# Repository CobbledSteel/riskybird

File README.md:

# RiskyBird for ROAR-Academy

This is the tutorial created by [Dima Nikiforov](https://www.linkedin.com/in/dima) and [Kris Dong](https://www.linkedin.com/in/chris-dong/) for ROAR Academy. The material has been taught at the University of California, Berkeley, as part of Berkeley ROAR Racing curriculum to students who want to learn entry-level skills about:

* Introduction to Embedded Systems
* Machine Learning Programming on Edge device 
* Introduction to Robotics
* Scientific Programming and Quantization
* Deep Neural Networks (DNN)
* Reinforcement Learning (RL) 

The material has been made open source FOR NON-COMMERCIAL USE only. Please contact the author for any questions: <vnikiforov@berkeley.edu>, <krisdong@berkeley.edu>

## Basic Installation

Users of this course are recommended to install the following software packages. The packages have been tested on Windows 10 and above, Mac OSX, and Ubuntu Linux systems.

* Python 3.8 via Miniconda (conda): <https://docs.conda.io/en/latest/miniconda.html>
* Git: <https://git-scm.com/book/en/v2/Getting-Started-Installing-Git>
* Visual Studio Code (code): <https://code.visualstudio.com/download>

**NOTE: If you are running conda and code in Windows, launching code from Anaconda Prompt will make sure that the conda environment available inside the integrated Terminal window. Otherwise you may encounter error that conda is not installed**

Once Python 3.8 is installed, the following Python modules can be installed using pip within the conda environment (for example, in (base) environment):
~~~
    python -m pip install numpy matplotlib
~~~

## Tensorflow Installation for Windows and Linux

For the DNN portion, we use tensorflow 2 and keras. The installation shall reference the official documentation: <https://www.tensorflow.org/install>. 

**Due to the fact that Google stopped supporing Windows Native environment above tensorflow 2.10, please make sure to install and use tensorflow 2.10 for compatibility with our tested code**

**If your PC comes with supported NVidia GPU for accelerating DNN code, please follow carefully the setup of GPU support for Linux and Windows Native. For MacOS, please read the instruction at the end**

After you have setup your system for an installation on either CPU or GPU, run the following pip script to install tensorflow 2.10
~~~
    pip install --upgrade pip
    pip install tensorflow==2.10
    pip install numpy==1.21
~~~

Finally, you may verify tensorflow has been properly set up by running the following test
~~~
    python -c "import tensorflow as tf; print(tf.reduce_sum(tf.random.normal([1000, 1000])))"
~~~

If you have install tensorflow with GPU support, you may verify by running the following test
~~~
    python -c "import tensorflow as tf; print(tf.config.list_physical_devices('GPU'))"
~~~

## Tensorflow Installation with Metal accelerated backend for MacOS

Apple has released a Metal-accelerated tensorflow backend to utilize the GPU on MacOS. Please visit Apple website to install tensorflow 2.10: <https://developer.apple.com/metal/tensorflow-plugin/>

## Installation of Reinforcement Learning Modules

This course will require installation of the following reinforcement learning modules:

* gym simulator: <https://github.com/openai/gym>
~~~
 pip install gym==0.17.3
 pip install pyglet==1.5.11
~~~

* gym-pybullet-drones simulator
~~~
 git submodule update --init --recursive
 cd sim/gym-pybullet-drones/
 pip3 install --upgrade pip
 pip3 install -e .
 pip3 install pyserial
~~~

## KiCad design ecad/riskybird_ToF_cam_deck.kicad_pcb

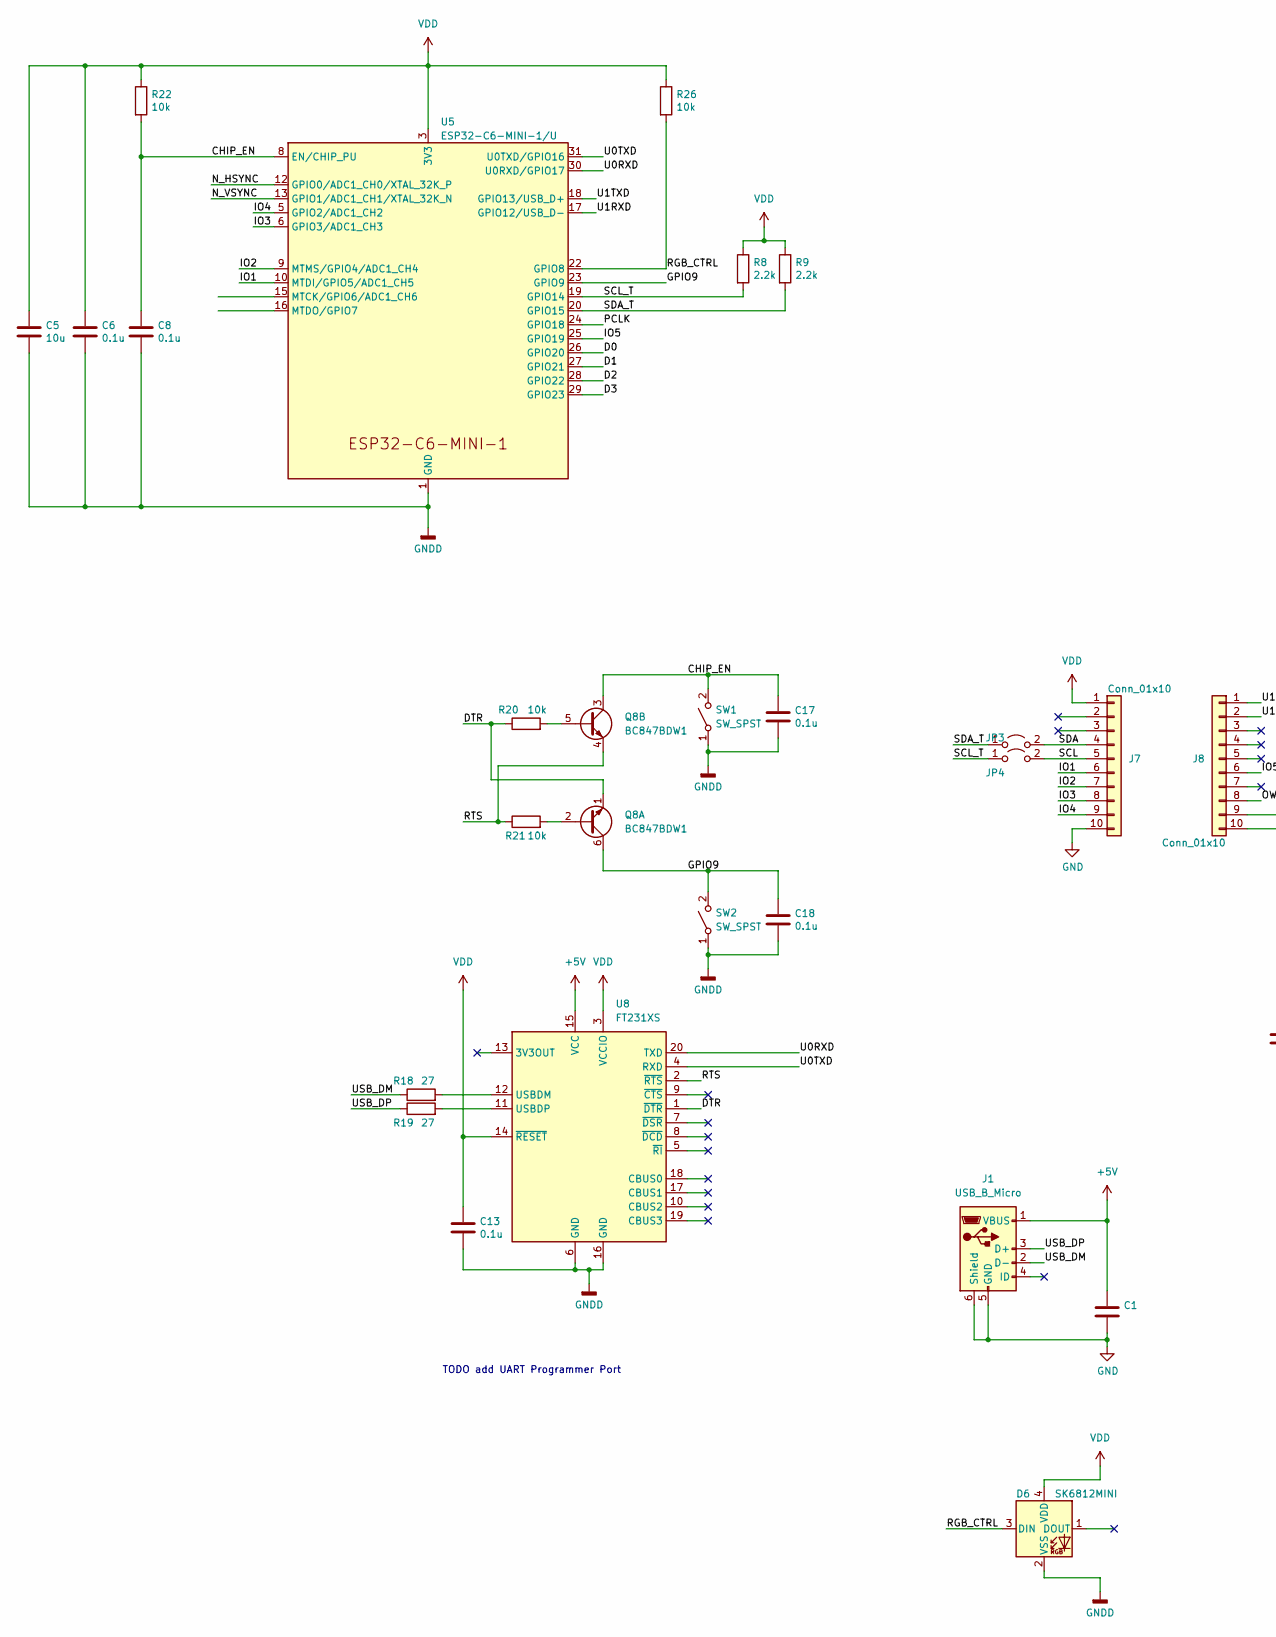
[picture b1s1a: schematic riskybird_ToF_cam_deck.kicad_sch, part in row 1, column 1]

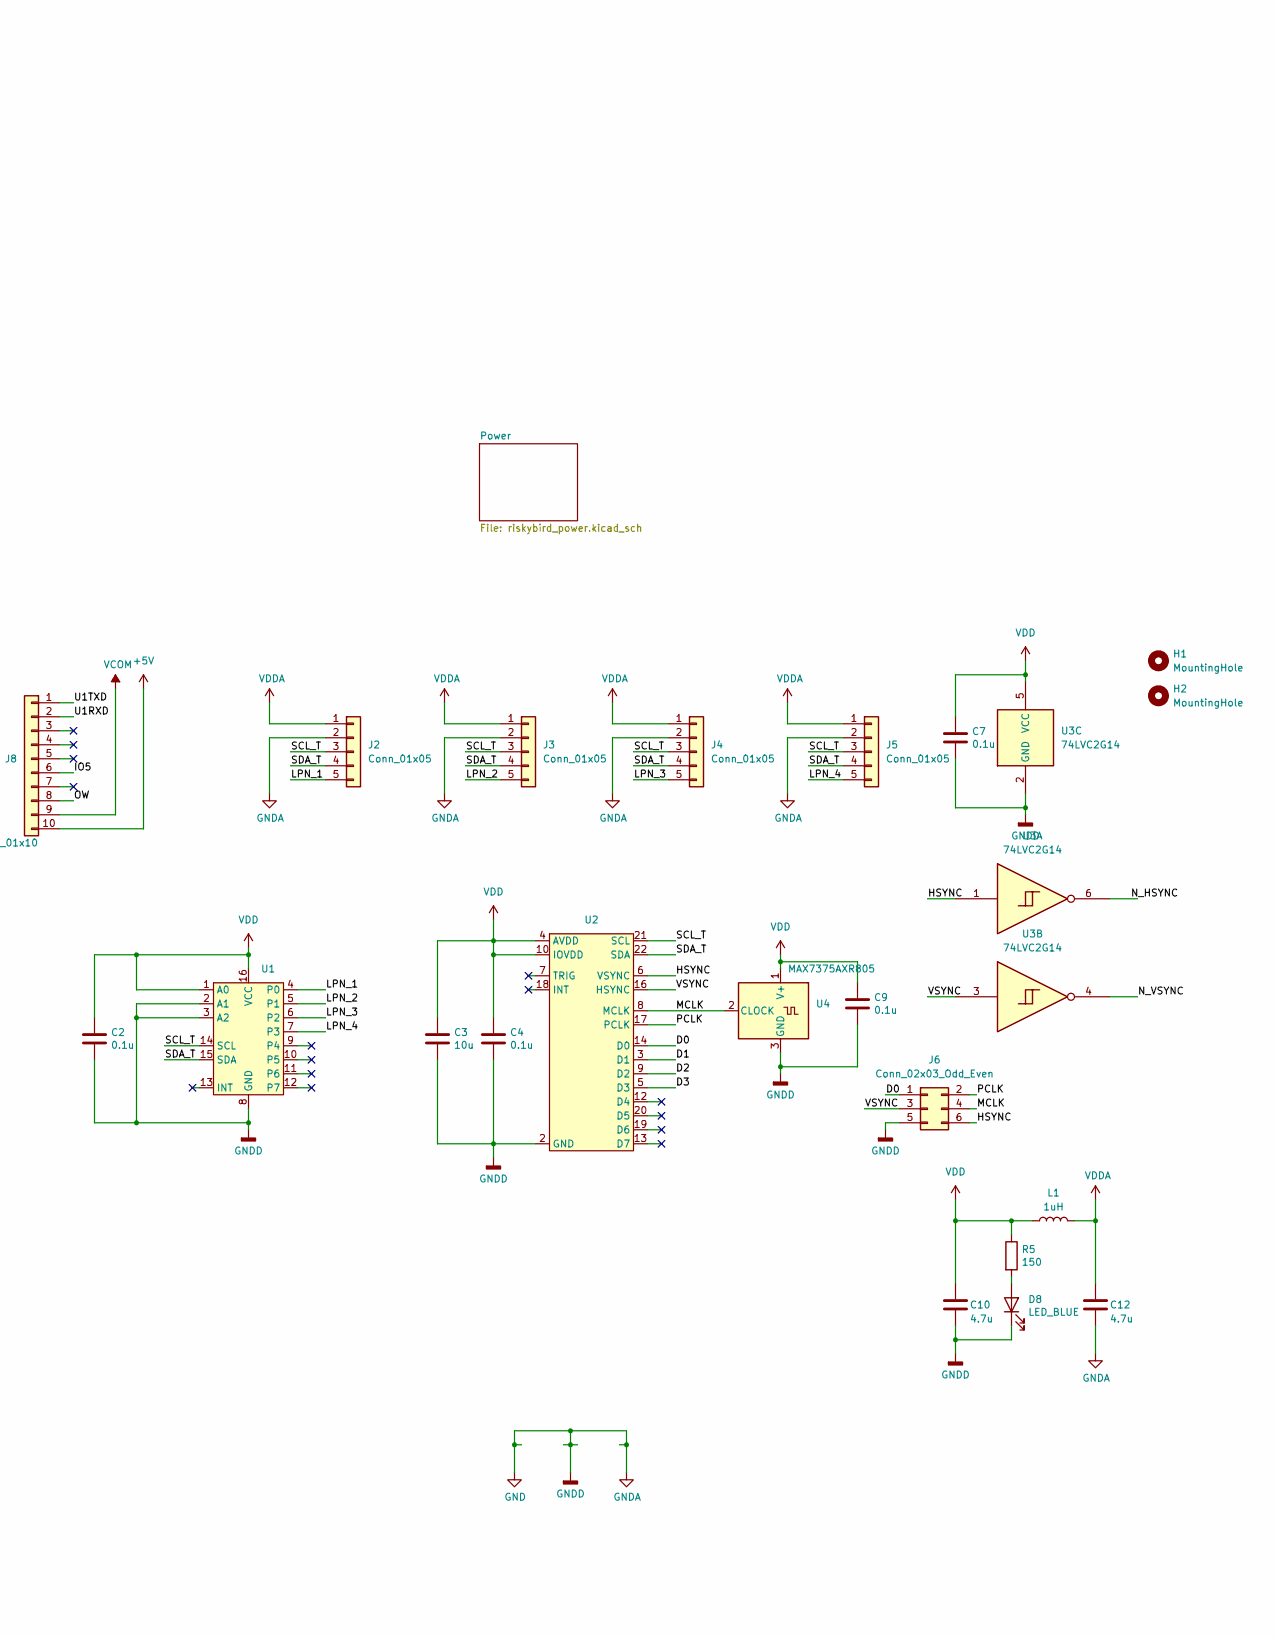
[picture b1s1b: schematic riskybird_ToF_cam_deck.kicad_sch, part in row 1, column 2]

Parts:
C1, C10, C12: 4.7u; C_0402_1005Metric
C2, C4, C6, C7, C8, C9, C13, C17, C18: 0.1u; C_0402_1005Metric
C3, C5: 10u; C_0402_1005Metric
D6: SK6812MINI; LED_SK6812MINI_PLCC4_3.5x3.5mm_P1.75mm
D8: LED_BLUE; LED_0805_2012Metric_Pad1.15x1.40mm_HandSolder
H1, H2: MountingHole; MountingHole_2.2mm_M2
J1: USB_B_Micro; USB_Micro-B_Molex_47346-0001
J2, J3, J4, J5: Conn_01x05; PinHeader_1x05_P2.54mm_Vertical
J6: Conn_02x03_Odd_Even; PinHeader_2x03_P1.27mm_Vertical
J7, J8: Conn_01x10; PinHeader_1x10_P2.00mm_Vertical_SMD_Pin1Right_THT
JP3, JP4: Jumper_2_Open; R_0402_1005Metric
L1: 1uH; L_0402_1005Metric
Q8: BC847BDW1; SOT-363_SC-70-6
R5: 150; R_0402_1005Metric
R8, R9: 2.2k; R_0402_1005Metric
R18, R19: 27; R_0402_1005Metric
R20, R21, R22, R26: 10k; R_0402_1005Metric
SW1, SW2: SW_SPST; SW_SPST_B3U-1000P
U1: TSSOP-16_4.4x5mm_P0.65mm
U2: SFV24R-1STE1LF
U3: 74LVC2G14; SOT-23-6
U4: MAX7375AXR805; SOT-323_SC-70
U5: ESP32-C6-MINI-1/U; ESP32-C6-MINI-1
U8: FT231XS; SSOP-20_3.9x8.7mm_P0.635mm

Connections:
+5V: C1.1, J1.1 (VBUS), J8.10, U8.15 (VCC)
/CHIP_EN: C8.1, C17.1, Q8.3 (C2), R22.2, SW1.2 (B), U5.8 (EN/CHIP_PU)
/D0: J6.1, U2.14 (D0), U5.26 (GPIO20)
/D1: U2.3 (D1), U5.27 (GPIO21)
/D2: U2.9 (D2), U5.28 (GPIO22)
/D3: U2.5 (D3), U5.29 (GPIO23)
/DTR: Q8.1 (E1), R20.1, U8.1 (~DTR)
/GPIO9: C18.1, Q8.6 (C1), SW2.2 (B), U5.23 (GPIO9)
/HSYNC: J6.6, U2.6 (VSYNC), U3.1
/IO1: J7.6, U5.10 (MTDI/GPIO5/ADC1_CH5)
/IO2: J7.7, U5.9 (MTMS/GPIO4/ADC1_CH4)
/IO3: J7.8, U5.6 (GPIO3/ADC1_CH3)
/IO4: J7.9, U5.5 (GPIO2/ADC1_CH2)
/IO5: J8.6, U5.25 (GPIO19)
/LPN_1: J2.5, U1.4 (P0)
/LPN_2: J3.5, U1.5 (P1)
/LPN_3: J4.5, U1.6 (P2)
/LPN_4: J5.5, U1.7 (P3)
/MCLK: J6.4, U2.8 (MCLK), U4.2 (CLOCK)
/N_HSYNC: U3.6, U5.12 (GPIO0/ADC1_CH0/XTAL_32K_P)
/N_VSYNC: U3.4, U5.13 (GPIO1/ADC1_CH1/XTAL_32K_N)
/OW: J8.8
/PCLK: J6.2, U2.17 (PCLK), U5.24 (GPIO18)
/RGB_CTRL: D6.3 (DIN), R26.2, U5.22 (GPIO8)
/RTS: Q8.4 (E2), R21.1, U8.2 (~RTS)
/SCL: J7.5, JP4.2 (B)
/SCL_T: J2.3, J3.3, J4.3, J5.3, JP4.1 (A), R8.2, U1.14 (SCL), U2.21 (SCL), U5.19 (GPIO14)
/SDA: J7.4, JP3.2 (B)
/SDA_T: J2.4, J3.4, J4.4, J5.4, JP3.1 (A), R9.2, U1.15 (SDA), U2.22 (SDA), U5.20 (GPIO15)
/U0RXD: U5.30 (U0RXD/GPIO17), U8.20 (TXD)
/U0TXD: U5.31 (U0TXD/GPIO16), U8.4 (RXD)
/U1RXD: J8.2, U5.17 (GPIO12/USB_D-)
/U1TXD: J8.1, U5.18 (GPIO13/USB_D+)
/USB_DM: J1.2 (D-), R18.1
/USB_DP: J1.3 (D+), R19.1
/VSYNC: J6.3, U2.16 (HSYNC), U3.3
GND: C1.2, C2.2, C3.2, C4.2, C5.2, C6.2, C7.2, C8.2, C9.2, C10.2, C12.2, C13.2, C17.2, C18.2, D6.2 (VSS), D8.1 (K), J1.5 (GND), J1.6 (Shield), J2.2, J3.2, J4.2, J5.2, J6.5, J7.10, SW1.1 (A), SW2.1 (A), U1.2 (A1), U1.3 (A2), U1.8 (GND), U2.2 (GND), U3.2 (GND), U4.3 (GND), U5.1 (GND), U5.2 (GND), U5.11 (GND), U5.14 (GND), U5.36 (GND), U5.37 (GND), U5.38 (GND), U5.39 (GND), U5.40 (GND), U5.41 (GND), U5.42 (GND), U5.43 (GND), U5.44 (GND), U5.45 (GND), U5.46 (GND), U5.47 (GND), U5.48 (GND), U5.49 (GND), U5.50 (GND), U5.51 (GND), U5.52 (GND), U5.53 (GND), U8.6 (GND), U8.16 (GND)
unnamed: D8.2 (A), R5.2
unnamed: Q8.2 (B1), R21.2
unnamed: Q8.5 (B2), R20.2
unnamed: R18.2, U8.12 (USBDM)
unnamed: R19.2, U8.11 (USBDP)
VCOM: J8.9
VDD: C2.1, C3.1, C4.1, C5.1, C6.1, C7.1, C9.1, C10.1, C13.1, D6.4 (VDD), J7.1, L1.1, R5.1, R8.1, R9.1, R22.1, R26.1, U1.1 (A0), U1.16 (VCC), U2.4 (AVDD), U2.10 (IOVDD), U3.5 (VCC), U4.1 (V+), U5.3 (3V3), U8.3 (VCCIO), U8.14 (~RESET)
VDDA: C12.1, J2.1, J3.1, J4.1, J5.1, L1.2

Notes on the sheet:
TODO add UART Programmer Port

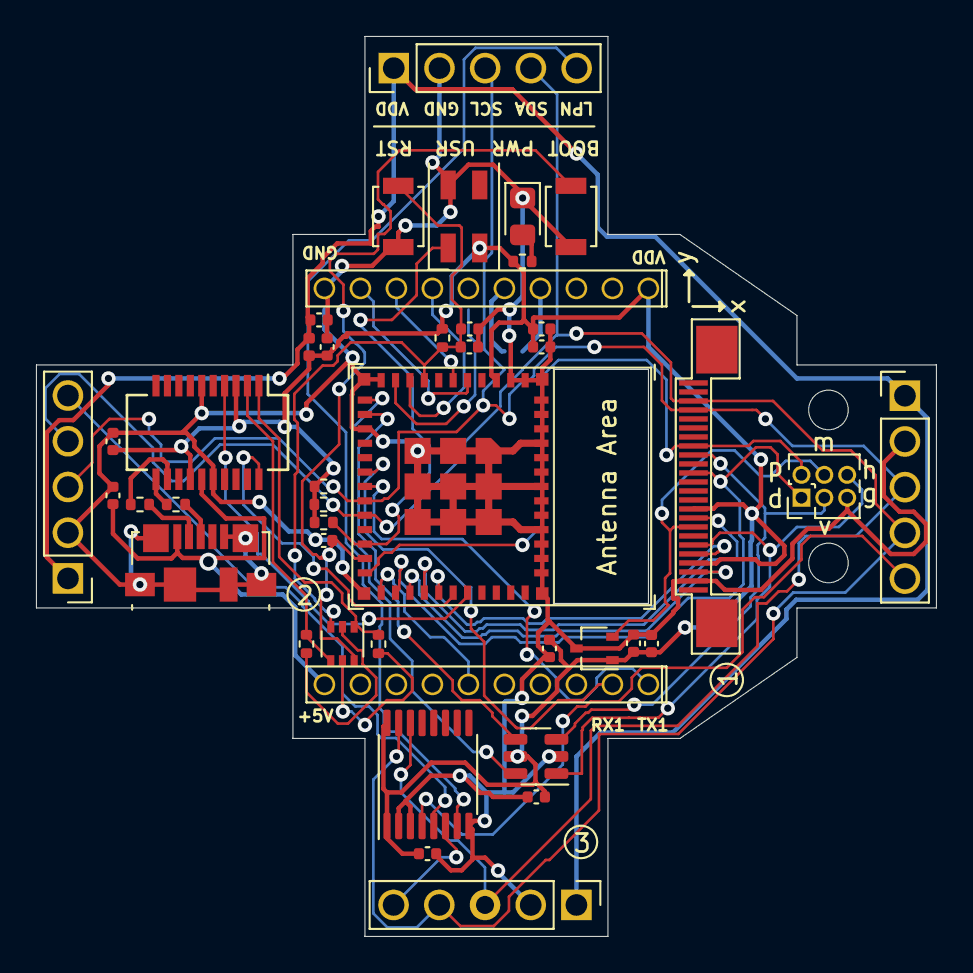
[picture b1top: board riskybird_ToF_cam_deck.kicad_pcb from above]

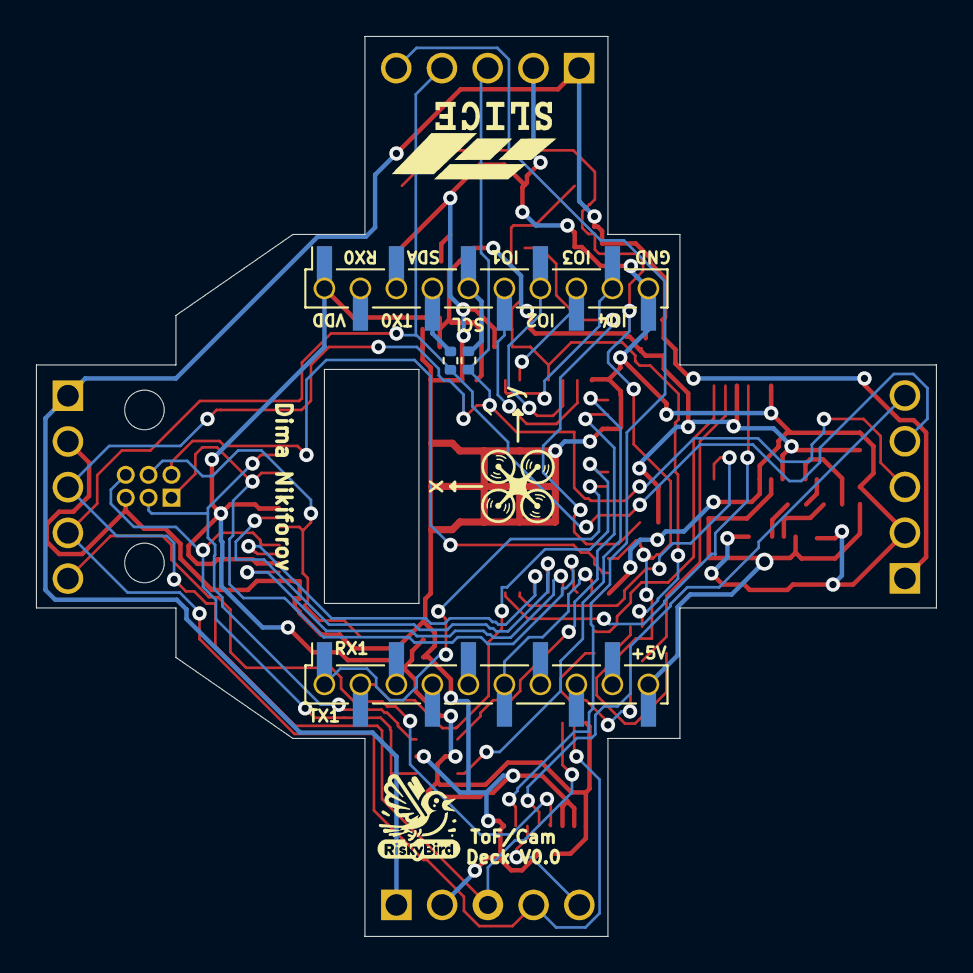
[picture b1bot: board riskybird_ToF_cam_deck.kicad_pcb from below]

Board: 2 copper layers, 50.0 x 50.0 mm, 47 parts (4 on the bottom side), 43 nets.

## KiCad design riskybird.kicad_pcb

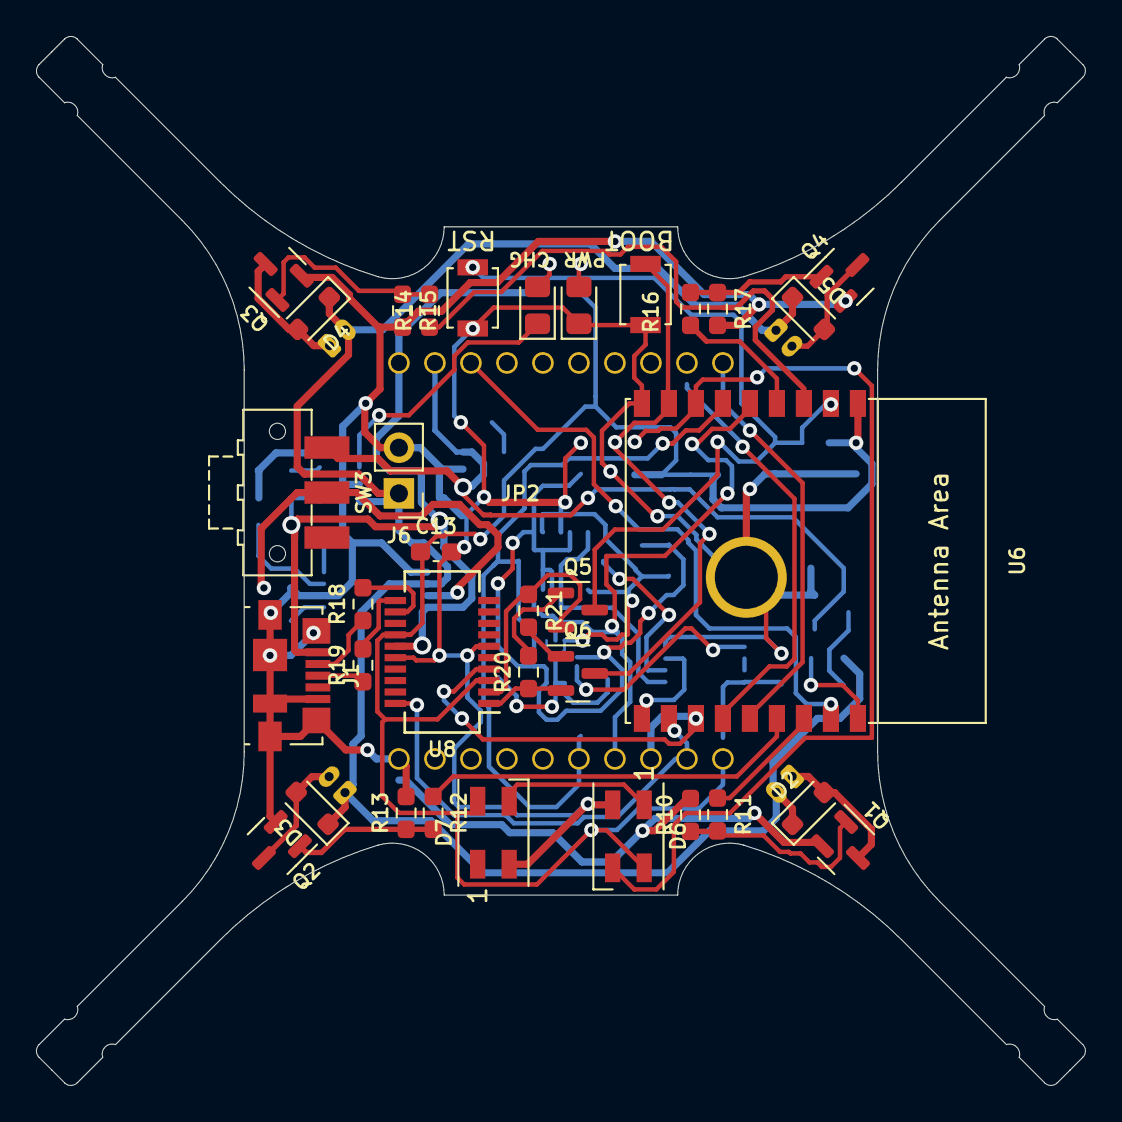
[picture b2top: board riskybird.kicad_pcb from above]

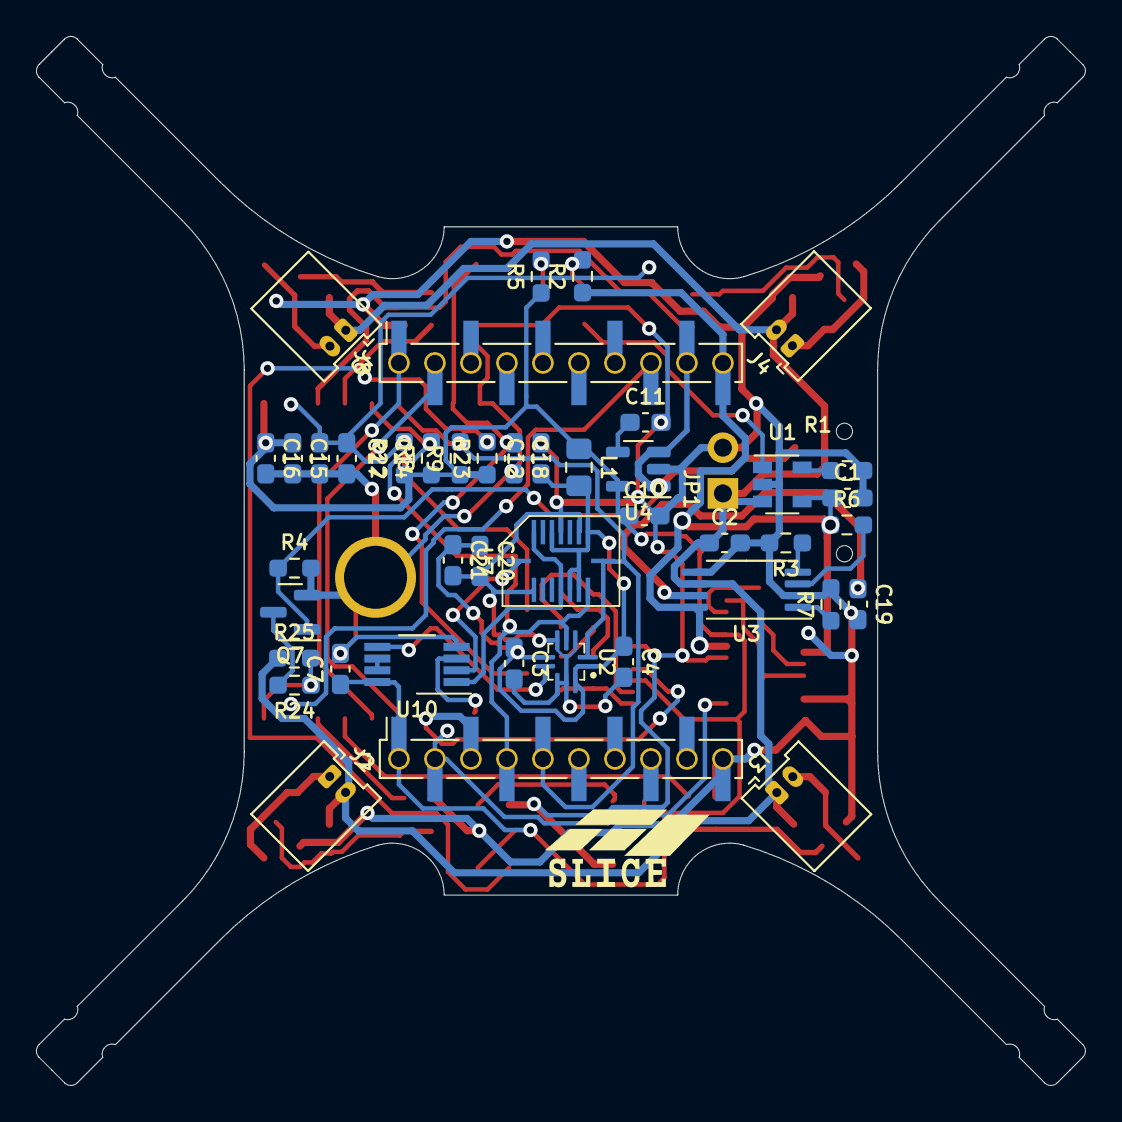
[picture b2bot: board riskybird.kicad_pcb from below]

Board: 2 copper layers, 58.3 x 58.3 mm, 80 parts (44 on the bottom side), 55 nets.

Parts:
C1, C2, C10, C12, C21: 4.7u; C_0603_1608Metric_Pad1.08x0.95mm_HandSolder
C3, C4: 100n; C_0603_1608Metric_Pad1.08x0.95mm_HandSolder
C7, C13, C14, C15, C17, C18: 0.1u; C_0603_1608Metric_Pad1.08x0.95mm_HandSolder
C11, C20: 10n; C_0603_1608Metric_Pad1.08x0.95mm_HandSolder
C16: 10u; C_0603_1608Metric_Pad1.08x0.95mm_HandSolder
C19: 1u; C_0603_1608Metric_Pad1.08x0.95mm_HandSolder
D1: LED_RED; LED_0805_2012Metric_Pad1.15x1.40mm_HandSolder
D2, D3, D4, D5: BAT54JFILM; D_SOD-323_HandSoldering
D6, D7: SK6812MINI; LED_SK6812MINI_PLCC4_3.5x3.5mm_P1.75mm
D8: LED_BLUE; LED_0805_2012Metric_Pad1.15x1.40mm_HandSolder
FID1: DroneFrame; riskybird_frame
J1: USB_B_Micro; USB_Micro-B_Molex_47346-0001
J2, J3, J4, J5: Conn_01x02; Molex_PicoBlade_53048-0210_1x02_P1.25mm_Horizontal
J6: Conn_01x02; PinHeader_1x02_P2.54mm_Vertical
J7, J8: Conn_01x10; PinHeader_1x10_P2.00mm_Vertical_SMD_Pin1Right_THT
JP1, JP2: SolderJumper_2_Bridged; shunt
L1: 1uH; L_0805_2012Metric_Pad1.15x1.40mm_HandSolder
Q1, Q2, Q3, Q4: SI2302; SOT-23
Q5, Q6: DNBT8105-7; SOT-23
Q7: Q_NMOS_GSD; SOT-23
R1: 2k; R_0603_1608Metric_Pad0.98x0.95mm_HandSolder
R2, R3, R5: 150; R_0603_1608Metric_Pad0.98x0.95mm_HandSolder
R4, R6, R7, R10, R13, R15, R17, R20, R21, R22, R23, R25: 10k; R_0603_1608Metric_Pad0.98x0.95mm_HandSolder
R8, R9: 2.2k; R_0603_1608Metric_Pad0.98x0.95mm_HandSolder
R11, R12, R14, R16: 47R; R_0603_1608Metric_Pad0.98x0.95mm_HandSolder
R18, R19: 27; R_0603_1608Metric_Pad0.98x0.95mm_HandSolder
R24: 20k; R_0603_1608Metric_Pad0.98x0.95mm_HandSolder
SW1, SW2: SW_SPST; SW_SPST_B3U-1000P
SW3: SW_SPST; SW_SPDT_CK-JS102011SAQN
U1: MCP73831-2-OT; SOT-23-5
U2: BMP390_Handsolder
U3: TPS2113A; TSSOP-8_4.4x3mm_P0.65mm
U4: LP2985-3.0; SOT-23-5
U6: ESP32-C3-WROOM-02
U7: BMI088; BMI088_Handsolder
U8: FT231XS; SSOP-20_3.9x8.7mm_P0.635mm
U10: 74LVC2G08; VSSOP-8_3.0x3.0mm_P0.65mm

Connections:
+5V: C1.1, J1.1 (VBUS), J8.10, R2.1, R6.1, U1.4 (VDD), U3.8 (IN1), U8.15 (VCC)
+BATT: C2.1, D2.1 (K), D3.1 (K), D4.1 (K), D5.1 (K), J2.2, J3.1, J4.2, J5.1, J6.1, R25.1, U1.3 (VBAT), U3.6 (IN2)
/CHIP_EN: C14.1, C17.1, Q5.3 (C), R22.2, SW1.2 (B), U6.2 (EN/CHIP_PU)
/DTR: Q6.2 (E), R20.1, U8.1 (~DTR)
/GPIO9: C18.1, Q6.3 (C), SW2.2 (B), U6.8 (GPIO9)
/INT_ACC: U7.16 (INT1), U10.2
/INT_ACC_GYR_BARO: U6.10 (GPIO10), U10.3
/INT_BARO: U2.7 (INT), U10.5
/INT_GYR: U7.1 (INT2), U7.12 (INT3), U10.1
/MOTOR1: R11.1, U6.16 (GPIO2/ADC1_CH2)
/MOTOR2: R12.1, U6.15 (GPIO3/ADC1_CH3)
/MOTOR3: R14.1, U6.3 (GPIO4/ADC1_CH4)
/MOTOR4: R16.1, U6.4 (GPIO5/ADC2_CH0)
/OW: J8.8, U6.17 (GPIO1/ADC1_CH1/XTAL_32K_N)
/RGB_CTRL: D6.3 (DIN), R23.2, U6.7 (GPIO8)
/RTS: Q5.2 (E), R21.1, U8.2 (~RTS)
/SCL: J7.5, R9.2, U2.2 (SCL/SCK), U6.6 (GPIO7), U7.8 (SCL/SCK)
/SDA: J7.4, R8.2, U2.4 (SDA/SDI), U6.5 (GPIO6), U7.9 (SDA/SDI)
/U0RXD: J7.2, U6.11 (GPIO20/U0RXD), U8.20 (TXD)
/U0TXD: J7.3, U6.12 (GPIO21/U0TXD), U8.4 (RXD)
/U1RXD: J8.2, U6.13 (GPIO18/USB_D-)
/U1TXD: J8.1, U6.14 (GPIO19/USB_D+)
/USB_DM: J1.2 (D-), R18.1
/USB_DP: J1.3 (D+), R19.1
/VSENSE: R24.1, R25.2, U6.18 (GPIO0/ADC1_CH0/XTAL_32K_P)
GND: C1.2, C2.2, C19.2, J1.5 (GND), J1.6 (Shield), J6.2, J7.10, JP1.1 (A), Q1.2 (S), Q2.2 (S), Q3.2 (S), Q4.2 (S), R1.2, R3.2, R7.2, R10.2, R13.2, R15.2, R17.2, U1.2 (VSS), U3.2 (EN), U3.5 (GND), U4.2 (GND)
GNDA: C3.2, C4.2, C12.2, C20.2, C21.2, JP2.2 (B), U2.3 (VSS), U2.5 (ADR/SDO), U2.8 (VSS), U2.9 (VSS), U7.4 (GNDIO), U7.6 (GND), U7.15 (SDO1)
GNDD: C7.2, C10.2, C11.2, C13.2, C14.2, C15.2, C16.2, C17.2, C18.2, D6.2 (VSS), D7.2 (VSS), D8.1 (K), JP1.2 (B), JP2.1 (A), Q7.2 (S), R4.2, SW1.1 (A), SW2.1 (A), U6.9 (GND), U6.19 (GND), U8.6 (GND), U8.16 (GND), U10.4 (GND)
unnamed: D1.2 (A), R2.2
unnamed: D1.1 (K), U1.1 (STAT)
unnamed: D2.2 (A), J2.1, Q1.3 (D)
unnamed: D3.2 (A), J3.2, Q2.3 (D)
unnamed: D4.2 (A), J4.1, Q3.3 (D)
unnamed: D5.2 (A), J5.2, Q4.3 (D)
unnamed: D6.1 (DOUT), D7.3 (DIN)
unnamed: D8.2 (A), R5.2
unnamed: Q1.1 (G), R10.1, R11.2
unnamed: Q2.1 (G), R12.2, R13.1
unnamed: Q3.1 (G), R14.2, R15.1
unnamed: Q4.1 (G), R16.2, R17.1
unnamed: Q5.1 (B), R20.2
unnamed: Q6.1 (B), R21.2
unnamed: Q7.3 (D), R24.2
unnamed: C19.1, SW3.2 (B), U3.7 (OUT)
unnamed: R1.1, U1.5 (PROG)
unnamed: R3.1, U3.4 (ILIM)
unnamed: R7.1, U3.1 (STAT)
unnamed: R6.2, U3.3 (VSNS)
unnamed: C11.1, U4.4 (BP)
unnamed: R18.2, U8.12 (USBDM)
unnamed: R19.2, U8.11 (USBDP)
unnamed: U10.6, U10.7
VCOM: J8.9, Q7.1 (G), R4.1, SW3.1 (A), U4.1 (VIN), U4.3 (ON/~OFF)
VDD: C7.1, C10.1, C13.1, C15.1, C16.1, D6.4 (VDD), D7.4 (VDD), J7.1, L1.1, R5.1, R8.1, R9.1, R22.1, R23.1, U4.5 (VOUT), U6.1 (3V3), U8.3 (VCCIO), U8.14 (~RESET), U10.8 (VCC)
VDDA: C3.1, C4.1, C12.1, C20.1, C21.1, L1.2, U2.1 (VDDIO), U2.6 (CSB), U2.10 (VDD), U7.3 (VDD), U7.7 (PS), U7.10 (SDO2), U7.11 (VDDIO)

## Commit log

2023-07-15 add initial files
2023-07-15 add slice symbol library
2023-07-16 update schematic with USB-UART, IMU, and Power
2023-07-17 add baro footprint, switches, make passives 0603
2023-07-17 update drone frame drawing
2023-07-17 before switching IMU to BMI088
2023-07-18 add new BMI088 IMU
2023-07-18 update footprints, begin placement
2023-07-18 finish initial placement draft
2023-07-19 start routing
2023-07-19 almost done routing
2023-07-19 minor changes
2023-07-21 finish routing
2023-07-21 finish 0.0 version
2023-07-30 move to ecad directory
2023-08-01 add initial state estimation code
2023-08-01 update data printing
2023-08-01 update state estimation loop to run in under 6ms
2023-08-03 git push origin master
2023-08-05 update pid gains
2023-08-08 update code to support HIL simulation
2023-08-08 update default SSID
2023-08-10 rl_script_for_cartpool
2023-08-10 modify cartpole to be trianning only
2023-08-10 Generated c++ binary file from quantized tflite
2023-08-10 add example for reading JPEG/grayscale image from camera to opencv
2023-08-10 update to train in outer loop
2023-08-11 add hello world example
2023-08-11 rename hello world
2023-08-11 initial ppo example
2023-08-11 rename exercises
2023-08-11 add lab1
2023-08-11 quantized TensorFlow Lite model and cpp file
2023-08-11 reorginaze code structure
2023-08-11 add Lab 2
2023-08-11 Create Exercise - Person_Detection Algorithm
2023-08-11 Unit1: DNN for Embedded System
2023-08-11 Unit2: Arduino Basics.md
2023-08-11 add permanent counter storage example
2023-08-11 Create Unit3: Running ML on Arduino
2023-08-11 add xxd python replacement
2023-08-11 Update Unit3: Running ML on Arduino
2023-08-11 add person detector
2023-08-11 Incompleted Unit3
2023-08-11 Update Unit2: Arduino Basics.md
    update NVS example
2023-08-11 Generate cpp file from fully trained model(50 ep)
2023-08-11 create cartpole arduino agent sketch
2023-08-11 rename unit 3 to have markdown
2023-08-11 add riskybird control code
2023-08-11 simplify person detection code
2023-08-12 add cartpole gifs
2023-08-12 add riskybird simulator
2023-08-12 update gym code
2023-08-12 add port constant
2023-08-12 code cleanup and updates
2023-08-12 add rgb led example
2023-12-17 RiskyBird 0.1
2023-12-19 create riskybird ToF/camera deck
